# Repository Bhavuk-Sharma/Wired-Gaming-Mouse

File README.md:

# Wired-Gaming-Mouse
This contains all the files for PCB Board, Schematic and manufactured CAD model of a Wired Gaming Mouse.
The maouse is using ADNS-3050 optical sensor, C8051F34x MCU.

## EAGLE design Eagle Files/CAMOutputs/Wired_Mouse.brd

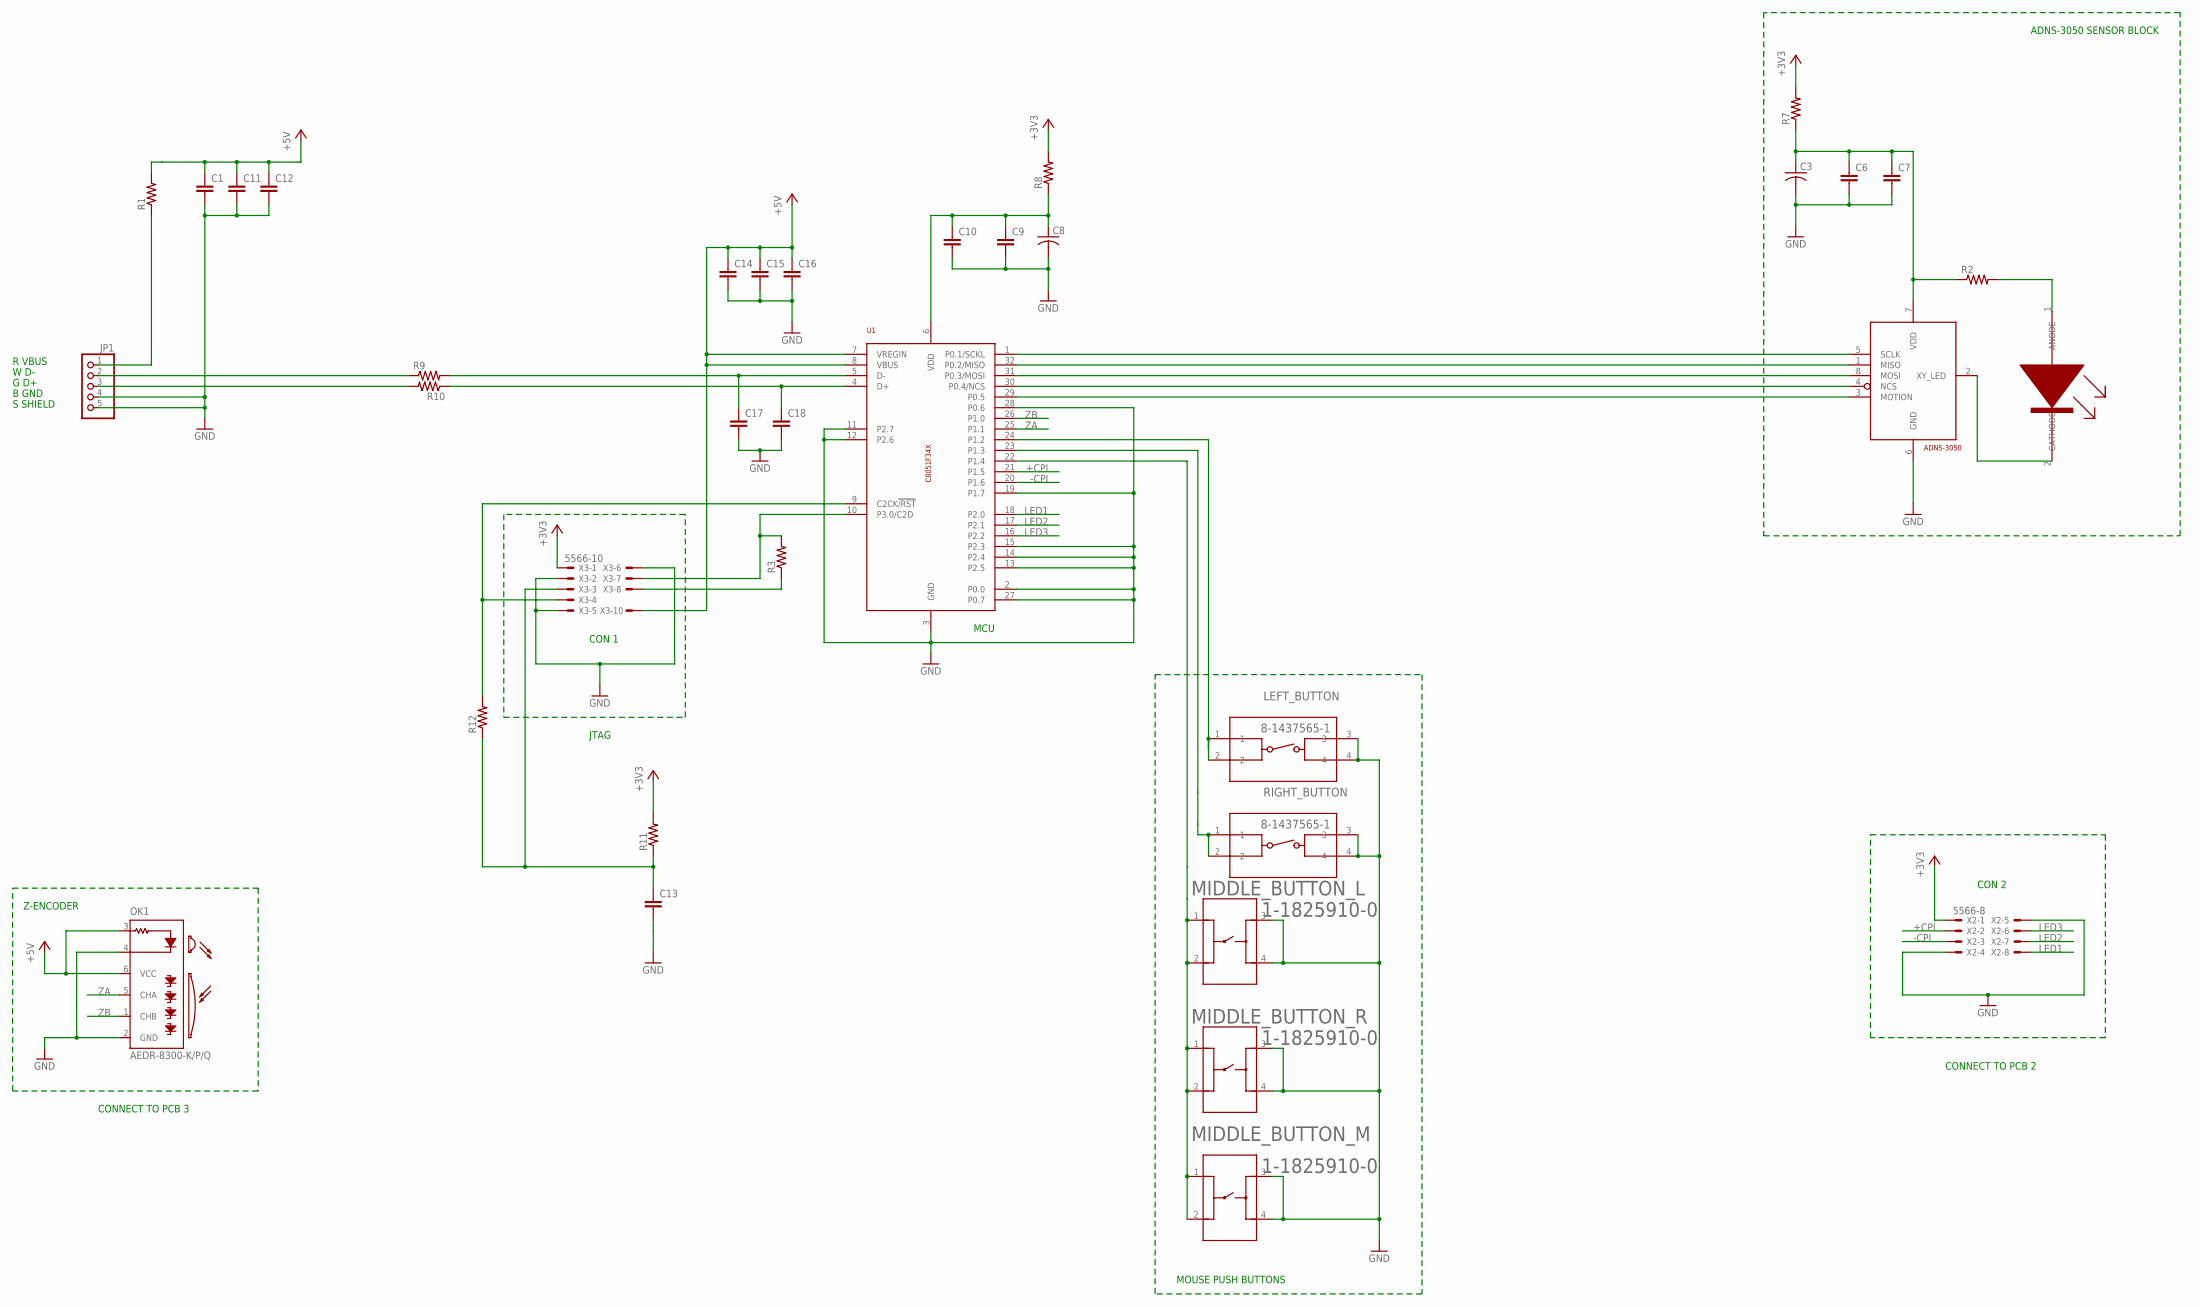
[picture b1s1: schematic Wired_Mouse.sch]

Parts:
C1, C6, C7, C9, C10, C11, C12, C13, C14, C15, C16, C17, C18: C-EUC0201; C0201
C3, C8: C-US025-025X050; C025-025X050
JP1: PINHD-1X5/90; 1X05/90
LEFT_BUTTON: 8-1437565-1; SW4_1437565
MIDDLE_BUTTON_L: 1-1825910-0; SWITCH_1-1825910-0
MIDDLE_BUTTON_M: 1-1825910-0; SWITCH_1-1825910-0
MIDDLE_BUTTON_R: 1-1825910-0; SWITCH_1-1825910-0
OK1: AEDR-8300-K/P/Q; AEDR-8300
R1, R2, R3, R7, R8, R9, R10, R11, R12: R-US_0204/7; 0204/7
RIGHT_BUTTON: 8-1437565-1; SW4_1437565
U$1: ADNS_3050THROUGH_HOLE; DIP1279W50P200L985H450Q8B
U$2: C8051F34XSURFACE-MOUNT; QFP80P900X900X160-32N
U$3: HLMP-EGXX_LEDTHROUGH_HOLE; LEDRD254W50D500H871B
X2: 5566-8
X3: 5566-10

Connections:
5V: JP1.1, R1.1
+3V3: R7.2, R8.2, R11.2, X2.1, X3.1
+5V: C1.1, C11.1, C12.1, C14.1, C15.1, C16.1, OK1.3 (A), OK1.6 (VCC), R1.2, U$2.7 (VREGIN), U$2.8 (VBUS), X3.10
+CPI: U$2.21 (P1.5), X2.2
-CPI: U$2.20 (P1.6), X2.3
GND: C1.2, C3.2, C6.2, C7.2, C8.2, C9.2, C10.2, C11.2, C12.2, C13.2, C14.2, C15.2, C16.2, C17.2, C18.2, JP1.4, JP1.5, LEFT_BUTTON.3, LEFT_BUTTON.4, MIDDLE_BUTTON_L.3, MIDDLE_BUTTON_L.4, MIDDLE_BUTTON_M.3, MIDDLE_BUTTON_M.4, MIDDLE_BUTTON_R.3, MIDDLE_BUTTON_R.4, OK1.2 (GND), OK1.4 (C), OK1.E1 (GND), OK1.E2 (GND), RIGHT_BUTTON.3, RIGHT_BUTTON.4, U$1.6 (GND), U$2.2 (P0.0), U$2.3 (GND), U$2.11 (P2.7), U$2.12 (P2.6), U$2.13 (P2.5), U$2.14 (P2.4), U$2.15 (P2.3), U$2.19 (P1.7), U$2.27 (P0.7), U$2.28 (P0.6), X2.4, X2.5, X3.2, X3.5, X3.6
LED1: U$2.18 (P2.0), X2.8
LED2: U$2.17 (P2.1), X2.7
LED3: U$2.16 (P2.2), X2.6
unnamed: U$1.5 (SCLK), U$2.1 (P0.1/SCKL)
unnamed: U$1.1 (MISO), U$2.32 (P0.2/MISO)
unnamed: U$1.8 (MOSI), U$2.31 (P0.3/MOSI)
unnamed: U$1.4 (NCS), U$2.30 (P0.4/NCS)
unnamed: U$1.3 (MOTION), U$2.29 (P0.5)
unnamed: C8.1, C9.1, C10.1, R8.1, U$2.6 (VDD)
unnamed: R2.2, U$3.1 (ANODE)
unnamed: U$1.2 (XY_LED), U$3.2 (CATHODE)
unnamed: C3.1, C6.1, C7.1, R2.1, R7.1, U$1.7 (VDD)
unnamed: LEFT_BUTTON.1, LEFT_BUTTON.2, U$2.24 (P1.2)
unnamed: RIGHT_BUTTON.1, RIGHT_BUTTON.2, U$2.23 (P1.3)
unnamed: JP1.2, R9.1
unnamed: MIDDLE_BUTTON_L.1, MIDDLE_BUTTON_L.2, MIDDLE_BUTTON_M.1, MIDDLE_BUTTON_M.2, MIDDLE_BUTTON_R.1, MIDDLE_BUTTON_R.2, U$2.22 (P1.4)
unnamed: JP1.3, R10.2
unnamed: C17.1, R9.2, U$2.5 (D-)
unnamed: C18.1, R10.1, U$2.4 (D+)
unnamed: R3.1, X3.8
unnamed: R3.2, U$2.10 (P3.0/C2D), X3.7
unnamed: R12.2, U$2.9 (C2CK!/RST), X3.4
unnamed: C13.1, R11.1, R12.1, X3.3
ZA: OK1.5 (CHA), U$2.25 (P1.1)
ZB: OK1.1 (CHB), U$2.26 (P1.0)

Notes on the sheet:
ADNS-3050 SENSOR BLOCK
MOUSE PUSH BUTTONS
R VBUS
W D-
G D+
B GND
S SHIELD
CON 1
JTAG
MCU
CON 2
CONNECT TO PCB 2
Z-ENCODER
CONNECT TO PCB 3

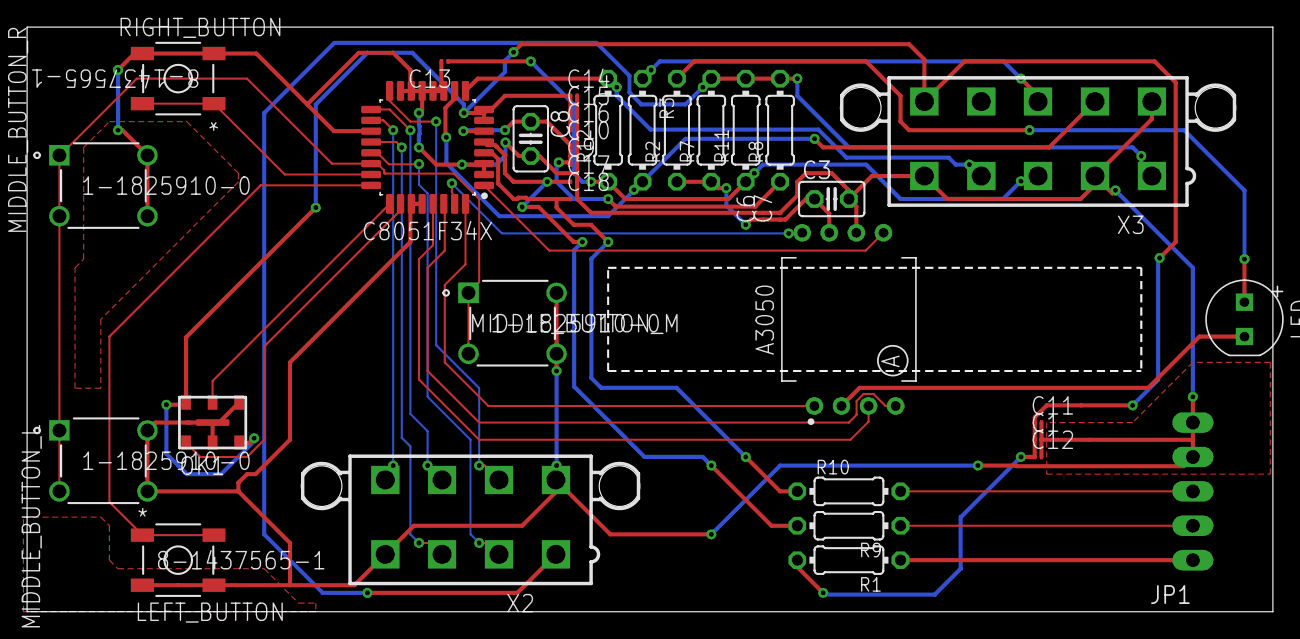
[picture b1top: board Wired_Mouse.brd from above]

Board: 2 copper layers, 91.8 x 43.0 mm, 36 parts (1 on the bottom side), 31 nets.

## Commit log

2020-04-05 Add files via upload
    This model was made using Autodesk Fusion 360.
2020-04-05 Create Avi file Details

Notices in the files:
parts and their libraries:
Switches: COPYRIGHT: Copyright (C) 2016 Accelerated Designs. All rights reserved
